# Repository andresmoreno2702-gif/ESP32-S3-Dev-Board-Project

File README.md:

# ESP32-S3 Dev Board — KiCad Project Files

Custom 4-layer ESP32-S3 development board designed in KiCad 9.
Manufactured by JLCPCB using the JLC04161H-3313 stackup.

## Contents
- /Schematic — KiCad schematic files
- /PCB — KiCad PCB layout files  
- /Gerbers — Manufacturing files for JLCPCB
- /BOM — Bill of materials

## Portfolio
Full project write-up: https://andresmoreno2702-gif.github.io/esp32-s3-project-main.html

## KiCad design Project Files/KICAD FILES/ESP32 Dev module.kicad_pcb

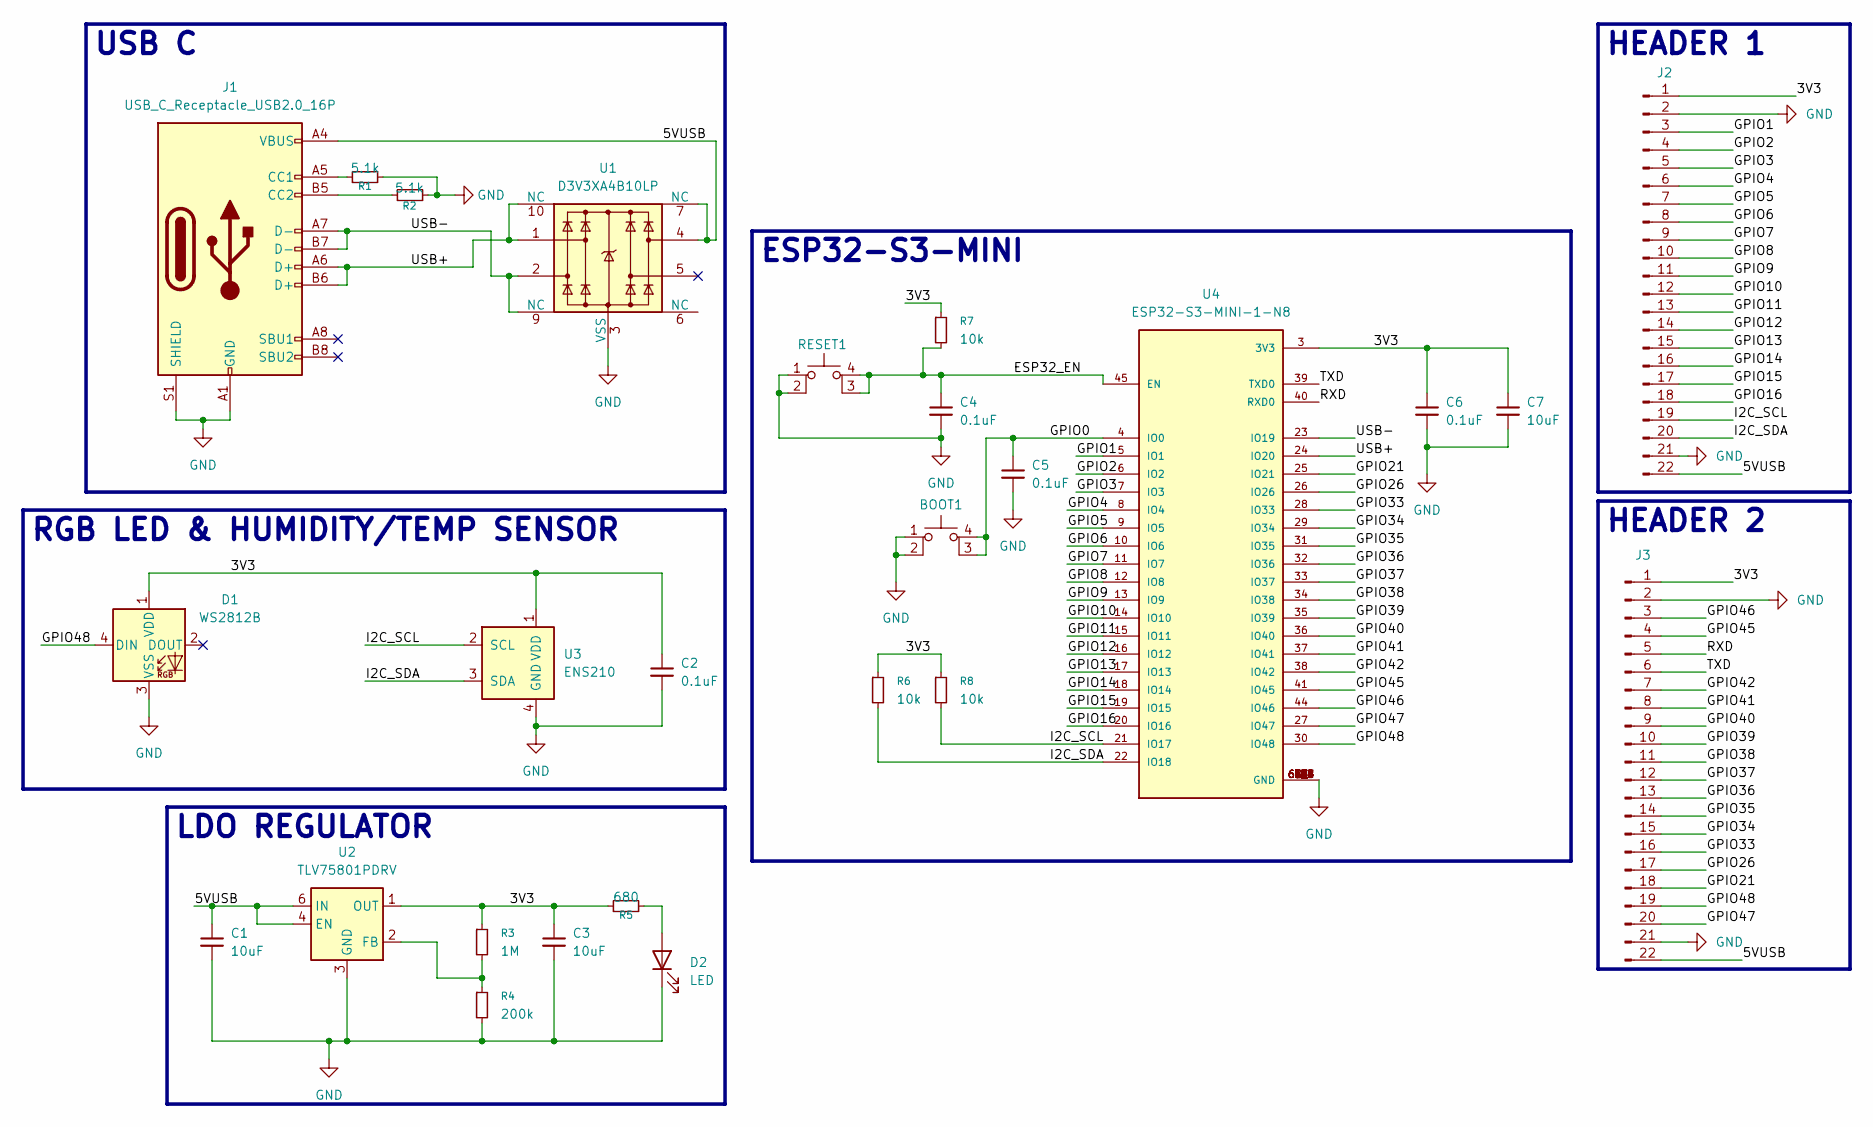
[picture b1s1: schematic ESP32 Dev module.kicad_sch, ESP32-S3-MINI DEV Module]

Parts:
BOOT1: SW_MEC_5E; PTS810SJG250SMTRLFS
C1, C3, C7: 10uF; C_0603_1608Metric_Pad1.08x0.95mm_HandSolder
C2, C4, C5, C6: 0.1uF; C_0603_1608Metric_Pad1.08x0.95mm_HandSolder
D1: WS2812B; LED_WS2812B_PLCC4_5.0x5.0mm_P3.2mm
D2: LED; LED_0603_1608Metric
J1: USB_C_Receptacle_USB2.0_16P; USB_C_Receptacle_GCT_USB4105-xx-A_16P_TopMnt_Horizontal
J2, J3: Conn_01x22_Pin; PinHeader_1x22_P2.54mm_Vertical
R1, R2: 5.1k; R_0603_1608Metric_Pad0.98x0.95mm_HandSolder
R3: 1M; R_0603_1608Metric_Pad0.98x0.95mm_HandSolder
R4: 200k; R_0603_1608Metric_Pad0.98x0.95mm_HandSolder
R5: 680; R_0603_1608Metric_Pad0.98x0.95mm_HandSolder
R6, R7, R8: 10k; R_0603_1608Metric_Pad0.98x0.95mm_HandSolder
RESET1: SW_MEC_5E; PTS810SJG250SMTRLFS
U1: D3V3XA4B10LP; Diodes_UDFN-10_1.0x2.5mm_P0.5mm
U2: TLV75801PDRV; WSON-6-1EP_2x2mm_P0.65mm_EP1x1.6mm
U3: ENS210; AMS_QFN-4-1EP_2x2mm_P0.95mm_EP0.7x1.6mm
U4: ESP32-S3-MINI-1-N8; PARTREV v0.6

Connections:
/3V3: C2.1, C3.1, C6.1, C7.1, D1.1 (VDD), J2.1, J3.1, R3.1, R5.1, R6.1, R7.1, R8.1, U2.1 (OUT), U3.1 (VDD), U4.3 (3V3)
/5VUSB: C1.1, J1.A4 (VBUS), J1.A9 (VBUS), J1.B4 (VBUS), J1.B9 (VBUS), J2.22, J3.22, U1.4, U1.7 (NC), U2.4 (EN), U2.6 (IN)
/ESP32_EN: C4.1, R7.2, RESET1.3 (K), RESET1.4 (A), U4.45 (EN)
/GPIO0: BOOT1.3 (K), BOOT1.4 (A), C5.1, U4.4 (IO0)
/GPIO1: J2.3, U4.5 (IO1)
/GPIO2: J2.4, U4.6 (IO2)
/GPIO3: J2.5, U4.7 (IO3)
/GPIO4: J2.6, U4.8 (IO4)
/GPIO5: J2.7, U4.9 (IO5)
/GPIO6: J2.8, U4.10 (IO6)
/GPIO7: J2.9, U4.11 (IO7)
/GPIO8: J2.10, U4.12 (IO8)
/GPIO9: J2.11, U4.13 (IO9)
/GPIO10: J2.12, U4.14 (IO10)
/GPIO11: J2.13, U4.15 (IO11)
/GPIO12: J2.14, U4.16 (IO12)
/GPIO13: J2.15, U4.17 (IO13)
/GPIO14: J2.16, U4.18 (IO14)
/GPIO15: J2.17, U4.19 (IO15)
/GPIO16: J2.18, U4.20 (IO16)
/GPIO21: J3.18, U4.25 (IO21)
/GPIO26: J3.17, U4.26 (IO26)
/GPIO33: J3.16, U4.28 (IO33)
/GPIO34: J3.15, U4.29 (IO34)
/GPIO35: J3.14, U4.31 (IO35)
/GPIO36: J3.13, U4.32 (IO36)
/GPIO37: J3.12, U4.33 (IO37)
/GPIO38: J3.11, U4.34 (IO38)
/GPIO39: J3.10, U4.35 (IO39)
/GPIO40: J3.9, U4.36 (IO40)
/GPIO41: J3.8, U4.37 (IO41)
/GPIO42: J3.7, U4.38 (IO42)
/GPIO45: J3.4, U4.41 (IO45)
/GPIO46: J3.3, U4.44 (IO46)
/GPIO47: J3.20, U4.27 (IO47)
/GPIO48: D1.4 (DIN), J3.19, U4.30 (IO48)
/I2C_SCL: J2.19, R8.2, U3.2 (SCL), U4.21 (IO17)
/I2C_SDA: J2.20, R6.2, U3.3 (SDA), U4.22 (IO18)
/RXD: J3.5, U4.40 (RXD0)
/TXD: J3.6, U4.39 (TXD0)
/USB+: J1.A6 (D+), J1.B6 (D+), U1.1, U1.10 (NC), U4.24 (IO20)
/USB-: J1.A7 (D-), J1.B7 (D-), U1.2, U1.9 (NC), U4.23 (IO19)
GND: BOOT1.1, BOOT1.2, C1.2, C2.2, C3.2, C4.2, C5.2, C6.2, C7.2, D1.3 (VSS), D2.1 (K), J1.A1 (GND), J1.A12 (GND), J1.B1 (GND), J1.B12 (GND), J1.S1 (SHIELD), J2.2, J2.21, J3.2, J3.21, R1.2, R2.2, R4.2, RESET1.1, RESET1.2, U1.3 (VSS), U1.8 (VSS), U2.3 (GND), U2.7 (GND), U3.4 (GND), U3.5 (GND), U4.1 (GND), U4.2 (GND), U4.42 (GND), U4.43 (GND), U4.46 (GND), U4.47 (GND), U4.48 (GND), U4.49 (GND), U4.50 (GND), U4.51 (GND), U4.52 (GND), U4.53 (GND), U4.54 (GND), U4.55 (GND), U4.56 (GND), U4.57 (GND), U4.58 (GND), U4.59 (GND), U4.60 (GND), U4.61 (GND), U4.61_1 (GND), U4.61_2 (GND), U4.61_3 (GND), U4.61_4 (GND), U4.61_5 (GND), U4.61_6 (GND), U4.61_7 (GND), U4.61_8 (GND), U4.62 (GND), U4.63 (GND), U4.64 (GND), U4.65 (GND)
unnamed: D2.2 (A), R5.2
unnamed: J1.A5 (CC1), R1.1
unnamed: J1.B5 (CC2), R2.1
unnamed: R3.2, R4.1, U2.2 (FB)

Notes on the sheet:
ESP32-S3-MINI
USB C
HEADER 1
LDO REGULATOR
RGB LED & HUMIDITY/TEMP SENSOR
HEADER 2

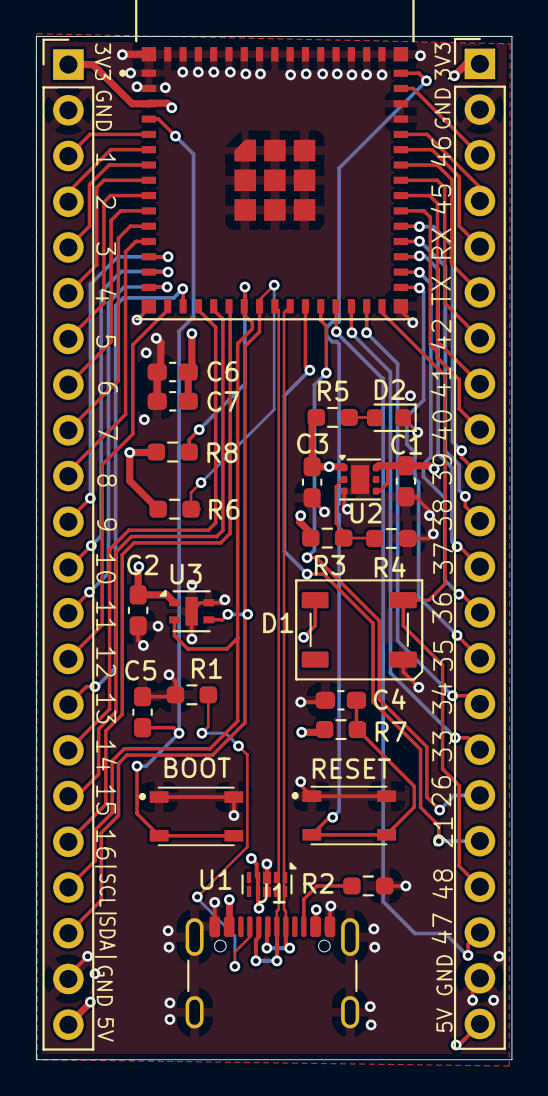
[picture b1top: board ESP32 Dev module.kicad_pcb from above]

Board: 4 copper layers, 26.4 x 56.8 mm, 26 parts (0 on the bottom side), 47 nets.

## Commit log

2026-04-10 Revise README with project details and structure
    Updated project title and added detailed description and contents.
2026-04-10 Add MIT License to the project
